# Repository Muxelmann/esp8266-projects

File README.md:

# ESP8266 Projects

This is a repository containing several MicroPyhton based projects that can be executed on the ESP8266. The latest MicroPython image for the EPS can be found [here](http://micropython.org/download/#esp8266). The current project is:

- EPS8266 SPI interface to ST7735 TFT screen
- *more to come...*

## ST7735 screen

A fast implementation using hardware SPI to send data to the ST7735 display. For more information refer to the folder's [README](https://github.com/Muxelmann/esp8266-projects/tree/master/st7735-tft) file.

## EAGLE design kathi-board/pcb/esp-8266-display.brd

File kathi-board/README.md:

# Kathi Board

## Details

This is a *surprise* present that uses the [ST7735 screen for ESP8266](https://github.com/Muxelmann/esp8266-projects/tree/master/st7735-tft) to:

1. Display graphics and text on the screen
2. Connects to one access point
3. Regularly downloads either:
	- Random images
	- Status updates
	- Recent images
4. Checks and installs (unfrozen) module updates

## Content

This folder contains both the `source`, `pcb` and `php` directories. These contain, respectively, the ES8266's source code, the EAGLE files to build the board, and the PHP webserver code.

## Functionality

The board code is a finite state machine that (once fully implemented) follows the following decision logic:

1. Start config webserver
2. Try connecting to a wifi from a `wifi.txt` list
3. If connected:
  1. Check for update -> update or continue
  2. Check for status -> display or continue
  3. Check for image -> display and wait
4. If not connected
  1. Display Wifi name
  2. Display personalised image

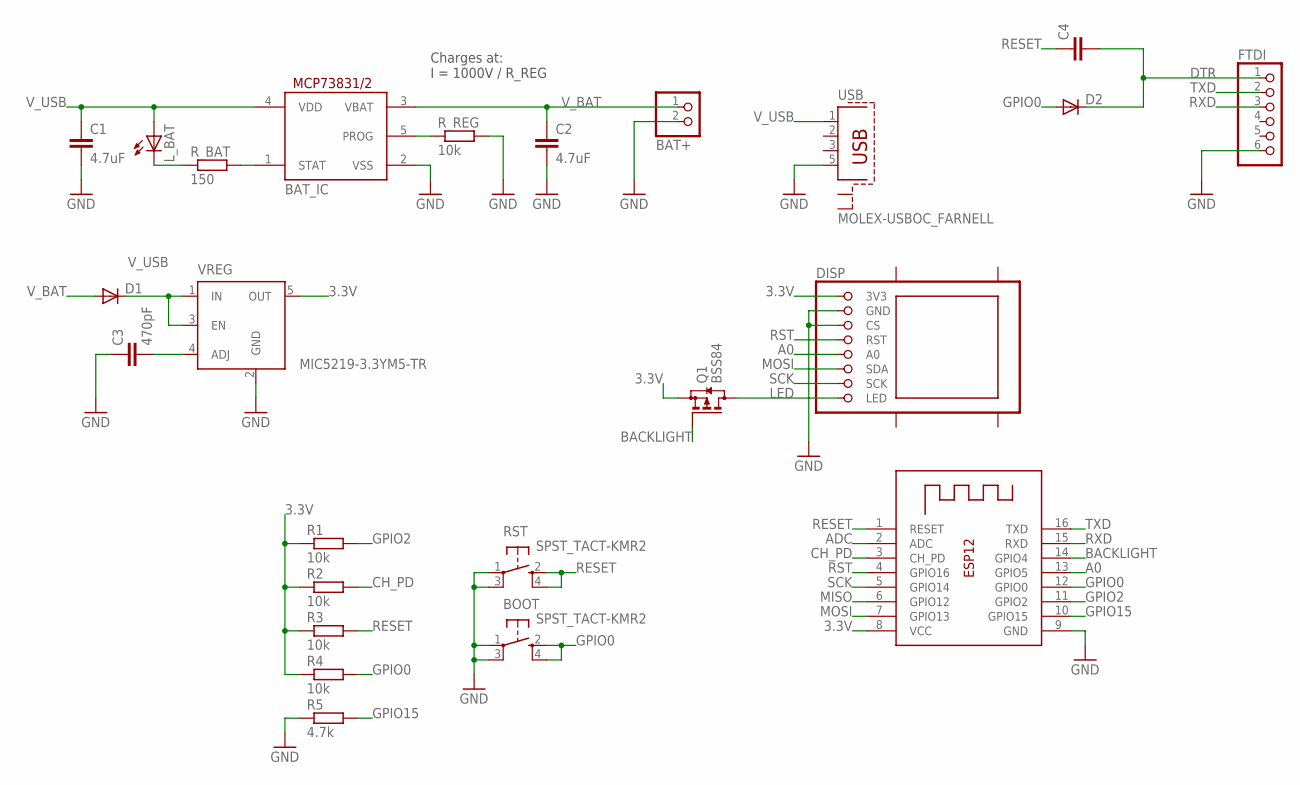
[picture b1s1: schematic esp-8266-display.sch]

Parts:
BAT+: JST_2PIN-SMT-RA; JST-PH-2-SMT-RA
BAT_IC: MCP73831/OT; SOT23-5L
BOOT: SPST_TACT-KMR2; KMR2
C1, C2: 4.7uF; C0603
C3: 470pF; C0603
C4: C-EUC0603; C0603
D1, D2: DIODE-SOD123; SOD123
DISP: TFT1.8; TFT01-1.8SP
FTDI: PINHD-1X6; 1X06
L_BAT: LEDCHIPLED_0603; CHIPLED_0603
Q1: BSS84; SOT23
R1, R2, R3, R4: 10k; R0603
R5: 4.7k; R0603
RST: SPST_TACT-KMR2; KMR2
R_BAT: 150; R0603
R_REG: 10k; R0603
USB: MOLEX-USBOC_FARNELL; MOLEX-105017
VREG: MIC5219-3.3YM5-TR; SOT23-5
X1: ESP-12

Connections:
3.3V: DISP.VCC (3V3), Q1.2 (S), R1.1, R2.1, R3.1, R4.1, VREG.5 (OUT), X1.8 (VCC)
A0: DISP.A0, X1.13 (GPIO5)
ADC: X1.2 (ADC)
BACKLIGHT: Q1.1 (G), X1.14 (GPIO4)
CH_PD: R2.2, X1.3 (CH_PD)
DTR: C4.2, D2.C, FTDI.1
GND: BAT+.2 (1), BAT_IC.2 (VSS), BOOT.1, BOOT.3 (P1), C1.2, C2.2, C3.1, DISP.CS, DISP.GND, FTDI.6, R5.1, RST.1, RST.3 (P1), R_REG.2, USB.5 (4), VREG.2 (GND), X1.9 (GND)
GPIO0: BOOT.2 (S), BOOT.4 (S1), D2.A, R4.2, X1.12 (GPIO0)
GPIO2: R1.2, X1.11 (GPIO2)
GPIO15: R5.2, X1.10 (GPIO15)
LED: DISP.LED, Q1.3 (D)
MISO: X1.6 (GPIO12)
MOSI: DISP.SDA, X1.7 (GPIO13)
unnamed: BAT_IC.1 (STAT), R_BAT.2
unnamed: L_BAT.C, R_BAT.1
unnamed: C3.2, VREG.4 (ADJ)
unnamed: BAT_IC.5 (PROG), R_REG.1
RESET: C4.1, R3.2, RST.2 (S), RST.4 (S1), X1.1 (RESET)
RST: DISP.RST, X1.4 (GPIO16)
RXD: FTDI.3, X1.15 (RXD)
SCK: DISP.SCK, X1.5 (GPIO14)
TXD: FTDI.2, X1.16 (TXD)
V_BAT: BAT+.1 (2), BAT_IC.3 (VBAT), C2.1, D1.A
V_USB: BAT_IC.4 (VDD), C1.1, D1.C, L_BAT.A, USB.1, VREG.1 (IN), VREG.3 (EN)

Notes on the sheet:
Charges at: I = 1000V / R_REG

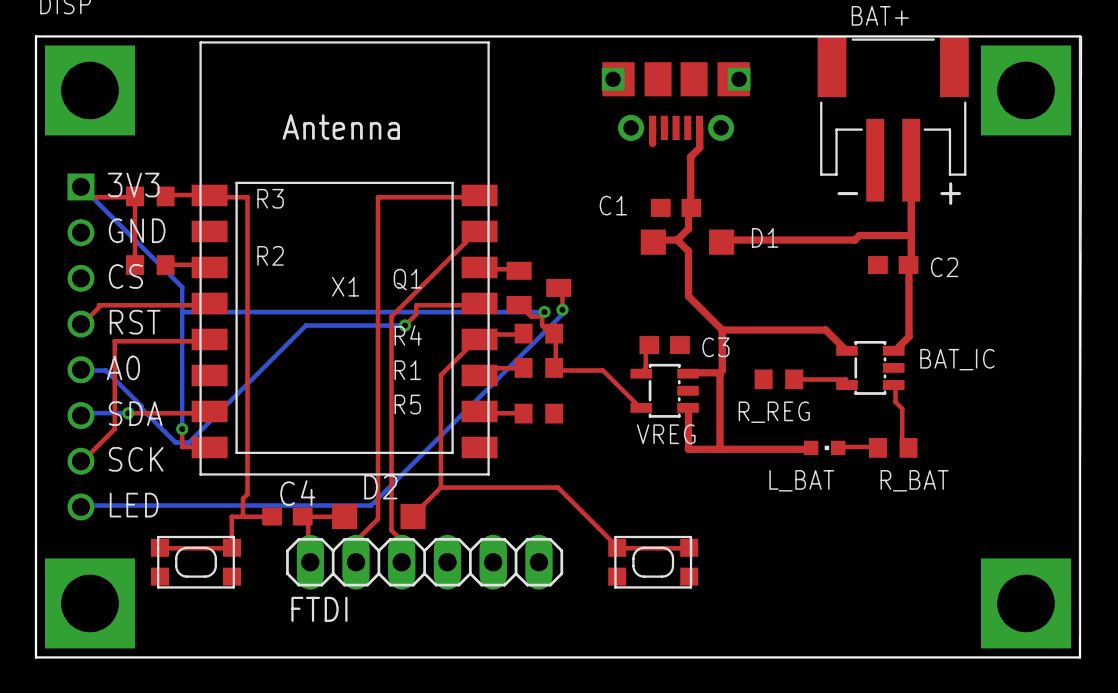
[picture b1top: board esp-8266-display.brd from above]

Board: 2 copper layers, 58.1 x 34.5 mm, 24 parts (0 on the bottom side), 22 nets.

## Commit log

2016-10-01 Maximising SPI buffer utilisation
    Rather than sending a few bytes at a time, the 1k SPI buffer is
    completely filled with a chunk of data. This significantly improves
    transfer speeds.
2016-10-01 Readme update
2016-10-01 Added text support
    Text support is now added. Also all unused commands are removed, and
    the SPI chunk size is reduced to 512kB.
2016-10-01 Added Bitmap support
    A sample bitmap is now plotted, too
2016-10-02 Removed comments and sped up BMP
    All redundant text has been removed to reduce the module size. Only the
    required parameters of the BMP are stored, and instead of pixel by
    pixel transmission, 64 pixels are sent in one go. The colour order had
    to be updated form BGR to RGB, which slows it down still. But that's
    pretty much it. Also, small changes can cause strange Memory Errors?!
2016-12-06 Starting Kathi project
2016-12-06 Assured connection order
2016-12-19 Added new source for project Kathi
2016-12-19 don't sync keys and images
2016-12-20 Webserver update
